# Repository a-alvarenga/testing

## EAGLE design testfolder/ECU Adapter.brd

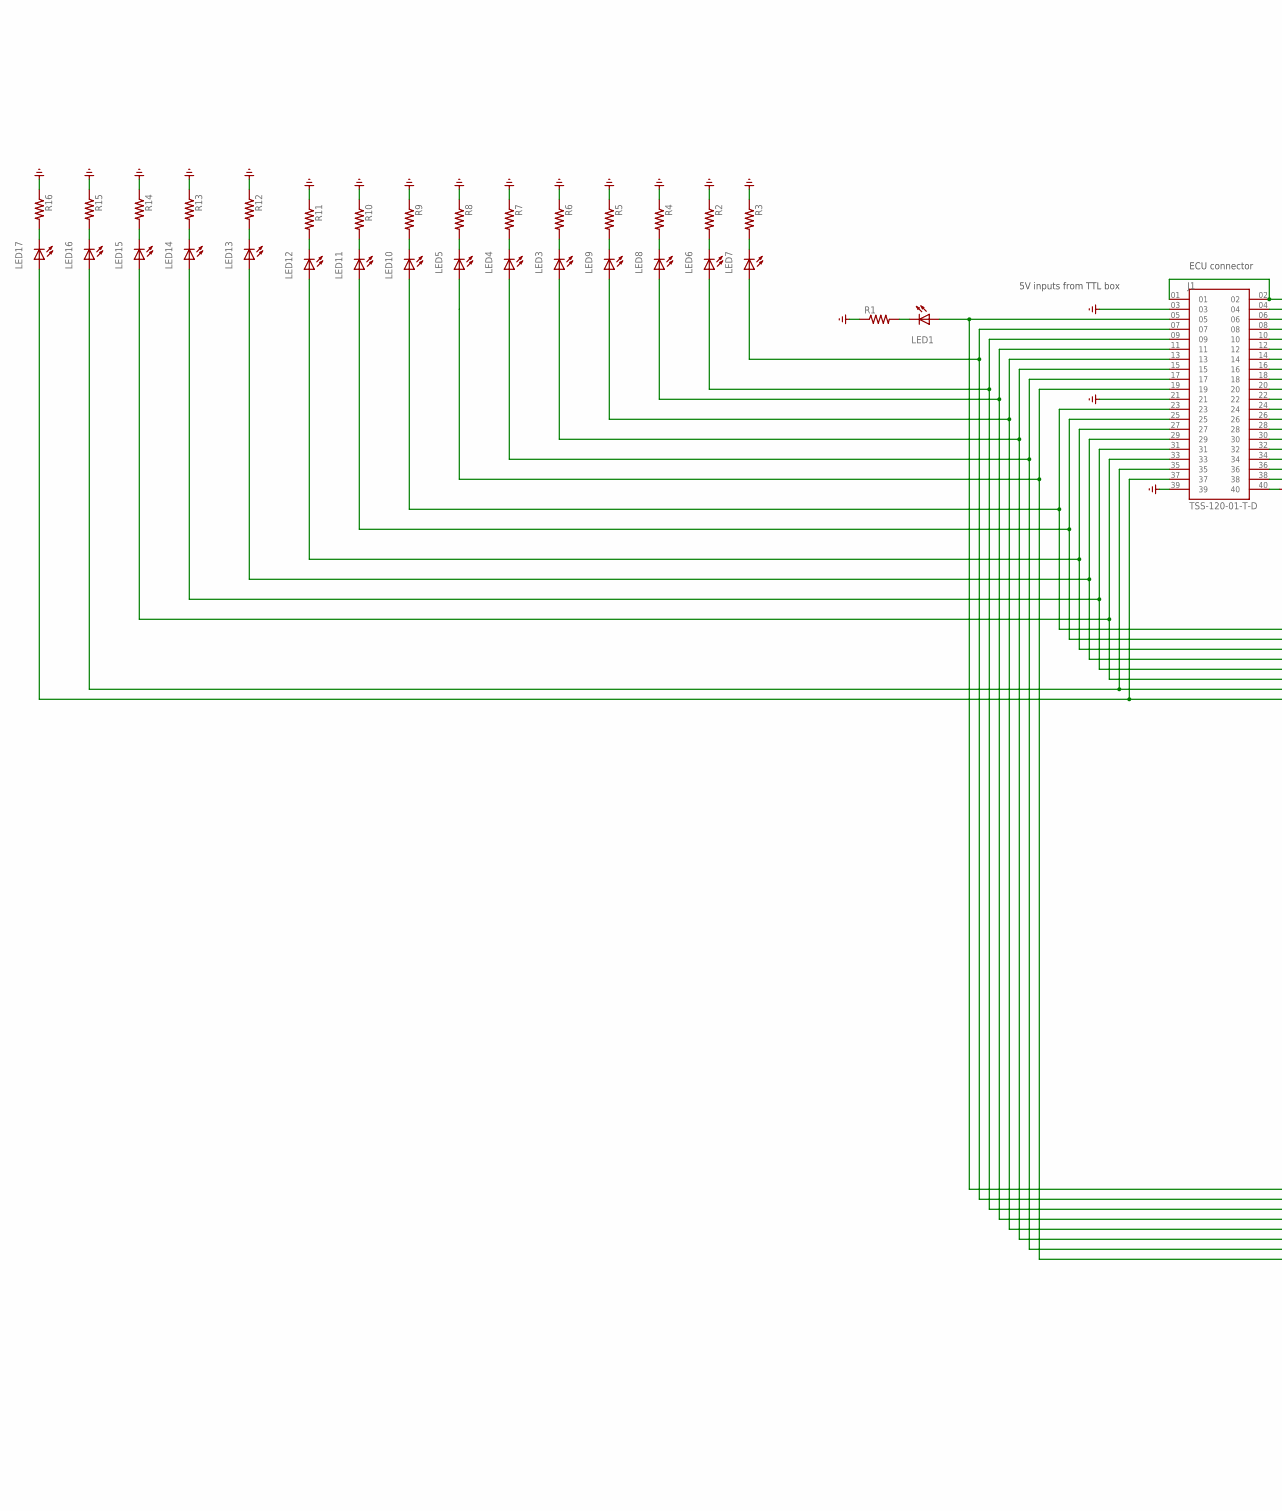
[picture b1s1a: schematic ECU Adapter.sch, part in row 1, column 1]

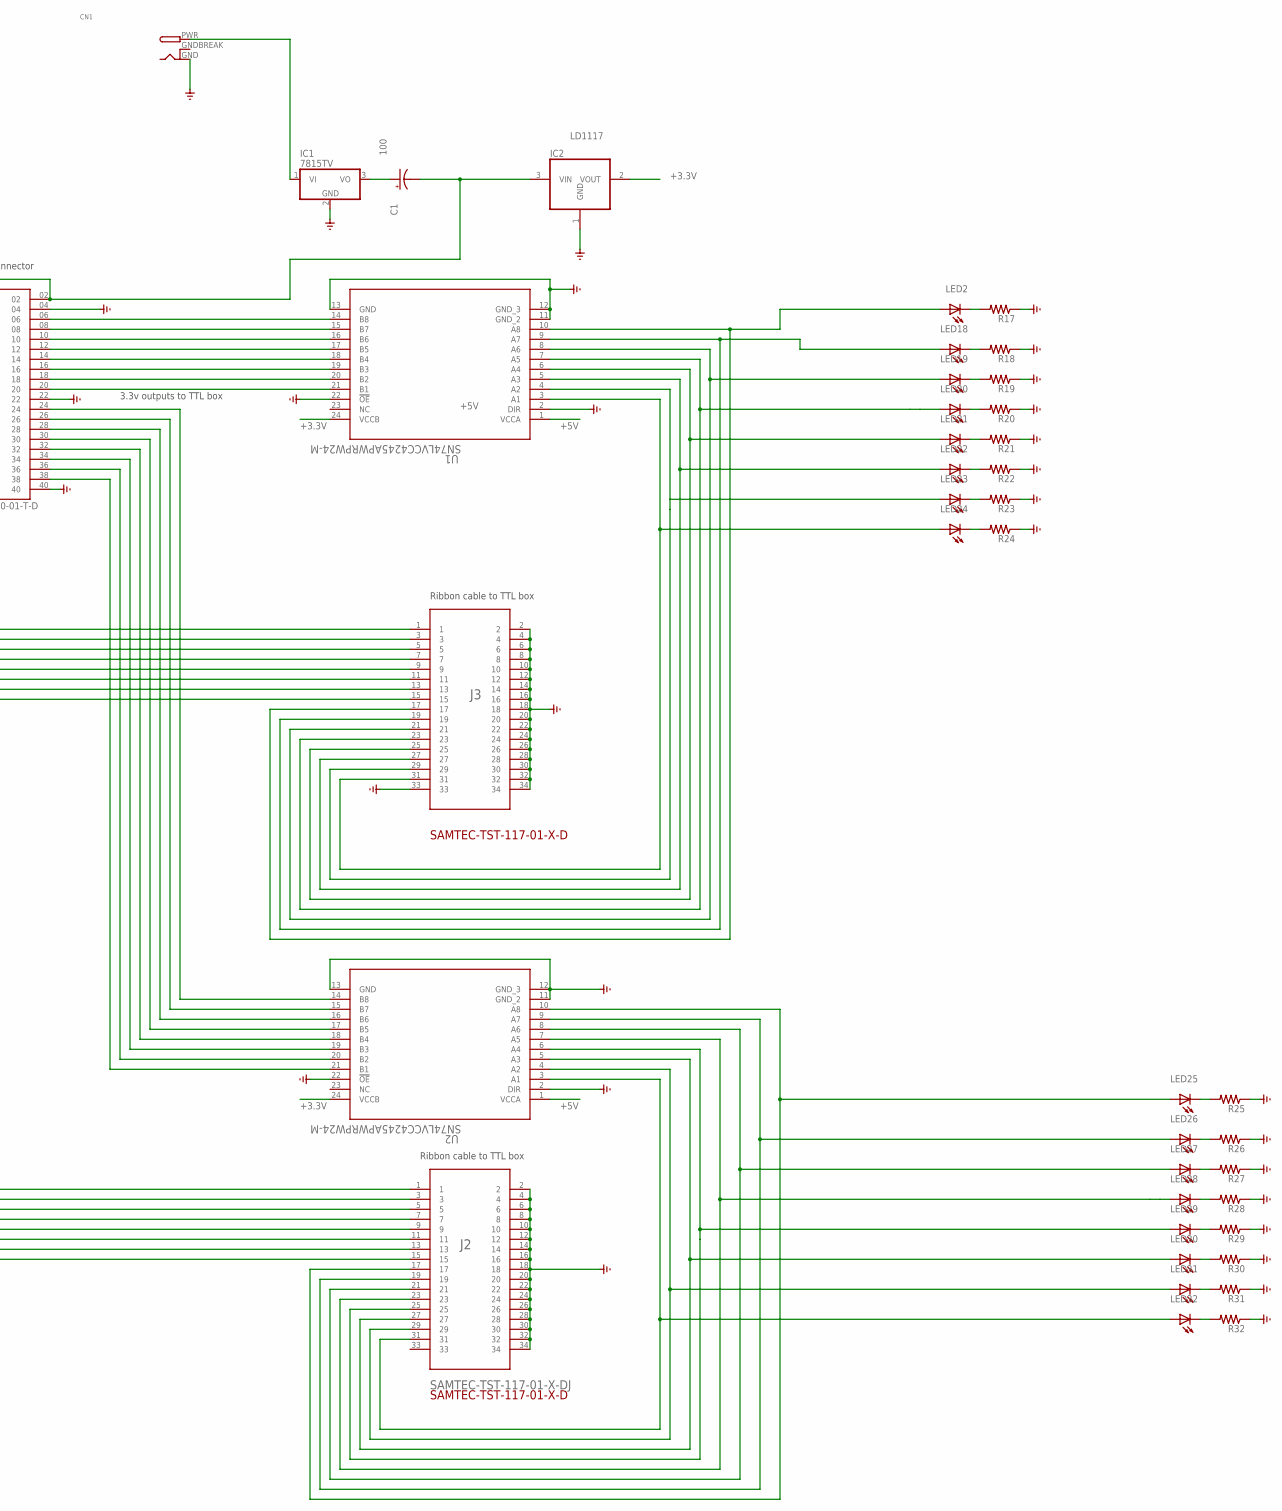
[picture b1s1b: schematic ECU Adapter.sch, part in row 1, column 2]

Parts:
C1: 100; E3,5-10
CN1: DCBARRELPTH; DCJACK_2MM_PTH
IC1: 7815TV; TO220V
IC2: LD1117; SOT223
J1: TSS-120-01-T-D; SAMTEC_TSS-120-01-T-D
J2, J3: SAMTEC-TST-117-01-X-DJ; SAMTEC-TST-117-01-X-D
LED1, LED2, LED3, LED4, LED5, LED6, LED7, LED8, LED9, LED10, LED11, LED12, LED13, LED14, LED15, LED16, LED17, LED18, LED19, LED20, LED21, LED22, LED23, LED24, LED25, LED26, LED27, LED28, LED29, LED30, LED31, LED32: LEDCHIPLED_0603; CHIPLED_0603
R1, R2, R3, R4, R5, R6, R7, R8, R9, R10, R11, R12, R13, R14, R15, R16, R17, R18, R19, R20, R21, R22, R23, R24, R25, R26, R27, R28, R29, R30, R31, R32: R-US_R0603; R0603
U1, U2: SN74LVCC4245APWRPW24-M; PW24-M

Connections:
+3.3V: IC2.2 (VOUT), U1.24 (VCCB), U2.24 (VCCB)
+5V: C1.-, IC2.3 (VIN), J1.01, J1.02, U1.1 (VCCA), U2.1 (VCCA)
GND: CN1.GND, IC1.2 (GND), IC2.1 (GND), J1.03, J1.04, J1.21, J1.22, J1.39, J1.40, J2.2, J2.4, J2.6, J2.8, J2.10, J2.12, J2.14, J2.16, J2.18, J2.20, J2.22, J2.24, J2.26, J2.28, J2.30, J2.32, J2.34, J3.2, J3.4, J3.6, J3.8, J3.10, J3.12, J3.14, J3.16, J3.18, J3.20, J3.22, J3.24, J3.26, J3.28, J3.30, J3.32, J3.33, J3.34, R1.1, R2.1, R3.1, R4.1, R5.1, R6.1, R7.1, R8.1, R9.1, R10.1, R11.1, R12.1, R13.1, R14.1, R15.1, R16.1, R17.1, R18.1, R19.1, R20.1, R21.1, R22.1, R23.1, R24.1, R25.1, R26.1, R27.1, R28.1, R29.1, R30.1, R31.1, R32.1, U1.2 (DIR), U1.11 (GND_2), U1.12 (GND_3), U1.13 (GND), U1.22 (!OE), U2.2 (DIR), U2.11 (GND_2), U2.12 (GND_3), U2.13 (GND), U2.22 (!OE)
GNDBREAK: CN1.GNDBREAK
unnamed: CN1.PWR, IC1.1 (VI)
unnamed: C1.+, IC1.3 (VO)
unnamed: J2.17, LED25.A, U2.10 (A8)
unnamed: LED25.C, R25.2
unnamed: LED26.C, R26.2
unnamed: J1.06, U1.14 (B8)
unnamed: J1.08, U1.15 (B7)
unnamed: J1.10, U1.16 (B6)
unnamed: J1.12, U1.17 (B5)
unnamed: J1.14, U1.18 (B4)
unnamed: J1.16, U1.19 (B3)
unnamed: J1.18, U1.20 (B2)
unnamed: J1.20, U1.21 (B1)
unnamed: LED27.C, R27.2
unnamed: J1.24, U2.14 (B8)
unnamed: J1.26, U2.15 (B7)
unnamed: J1.28, U2.16 (B6)
unnamed: J1.05, J2.1, LED1.A
unnamed: J1.29, J3.7, LED13.A
unnamed: LED13.C, R12.2
unnamed: J1.31, J3.9, LED14.A
unnamed: LED14.C, R13.2
unnamed: J1.33, J3.11, LED15.A
unnamed: LED15.C, R14.2
unnamed: J1.35, J3.13, LED16.A
unnamed: J2.19, LED26.A, U2.9 (A7)
unnamed: J2.21, LED27.A, U2.8 (A6)
unnamed: J2.25, LED29.A, U2.6 (A4)
unnamed: J2.27, LED30.A, U2.5 (A3)
unnamed: J2.29, LED31.A, U2.4 (A2)
unnamed: J2.31, LED32.A, U2.3 (A1)
unnamed: LED16.C, R15.2
unnamed: J3.17, LED2.A, U1.10 (A8)
unnamed: LED17.C, R16.2
unnamed: LED2.C, R17.2
unnamed: J2.23, LED28.A, U2.7 (A5)
unnamed: LED18.C, R18.2
unnamed: J3.21, LED19.A, U1.8 (A6)
unnamed: J1.37, J3.15, LED17.A
unnamed: J1.30, U2.17 (B5)
unnamed: J3.19, LED18.A, U1.9 (A7)
unnamed: J1.32, U2.18 (B4)
unnamed: LED28.C, R28.2
unnamed: J1.34, U2.19 (B3)
unnamed: J1.36, U2.20 (B2)
unnamed: J1.38, U2.21 (B1)
unnamed: LED1.C, R1.2
unnamed: J1.09, J2.5, LED6.A
unnamed: LED6.C, R2.2
unnamed: J1.07, J2.3, LED7.A
unnamed: LED7.C, R3.2
unnamed: J1.11, J2.7, LED8.A
unnamed: LED8.C, R4.2
unnamed: J1.13, J2.9, LED9.A
unnamed: LED9.C, R5.2
unnamed: J1.15, J2.11, LED3.A
unnamed: LED3.C, R6.2
unnamed: J1.17, J2.13, LED4.A
unnamed: LED4.C, R7.2
unnamed: J1.19, J2.15, LED5.A
unnamed: LED5.C, R8.2
unnamed: J1.23, J3.1, LED10.A
unnamed: LED10.C, R9.2
unnamed: J1.25, J3.3, LED11.A
unnamed: LED11.C, R10.2
unnamed: J1.27, J3.5, LED12.A
unnamed: LED12.C, R11.2
unnamed: LED19.C, R19.2
unnamed: J3.23, LED20.A, U1.7 (A5)
unnamed: LED20.C, R20.2
unnamed: J3.25, LED21.A, U1.6 (A4)
unnamed: LED21.C, R21.2
unnamed: J3.27, LED22.A, U1.5 (A3)
unnamed: LED22.C, R22.2
unnamed: J3.29, LED23.A, U1.4 (A2)
unnamed: LED23.C, R23.2
unnamed: J3.31, LED24.A, U1.3 (A1)
unnamed: LED24.C, R24.2
unnamed: LED29.C, R29.2
unnamed: LED30.C, R30.2
unnamed: LED31.C, R31.2
unnamed: LED32.C, R32.2

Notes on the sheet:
3.3v outputs to TTL box
5V inputs from TTL box
ECU connector
Ribbon cable to TTL box

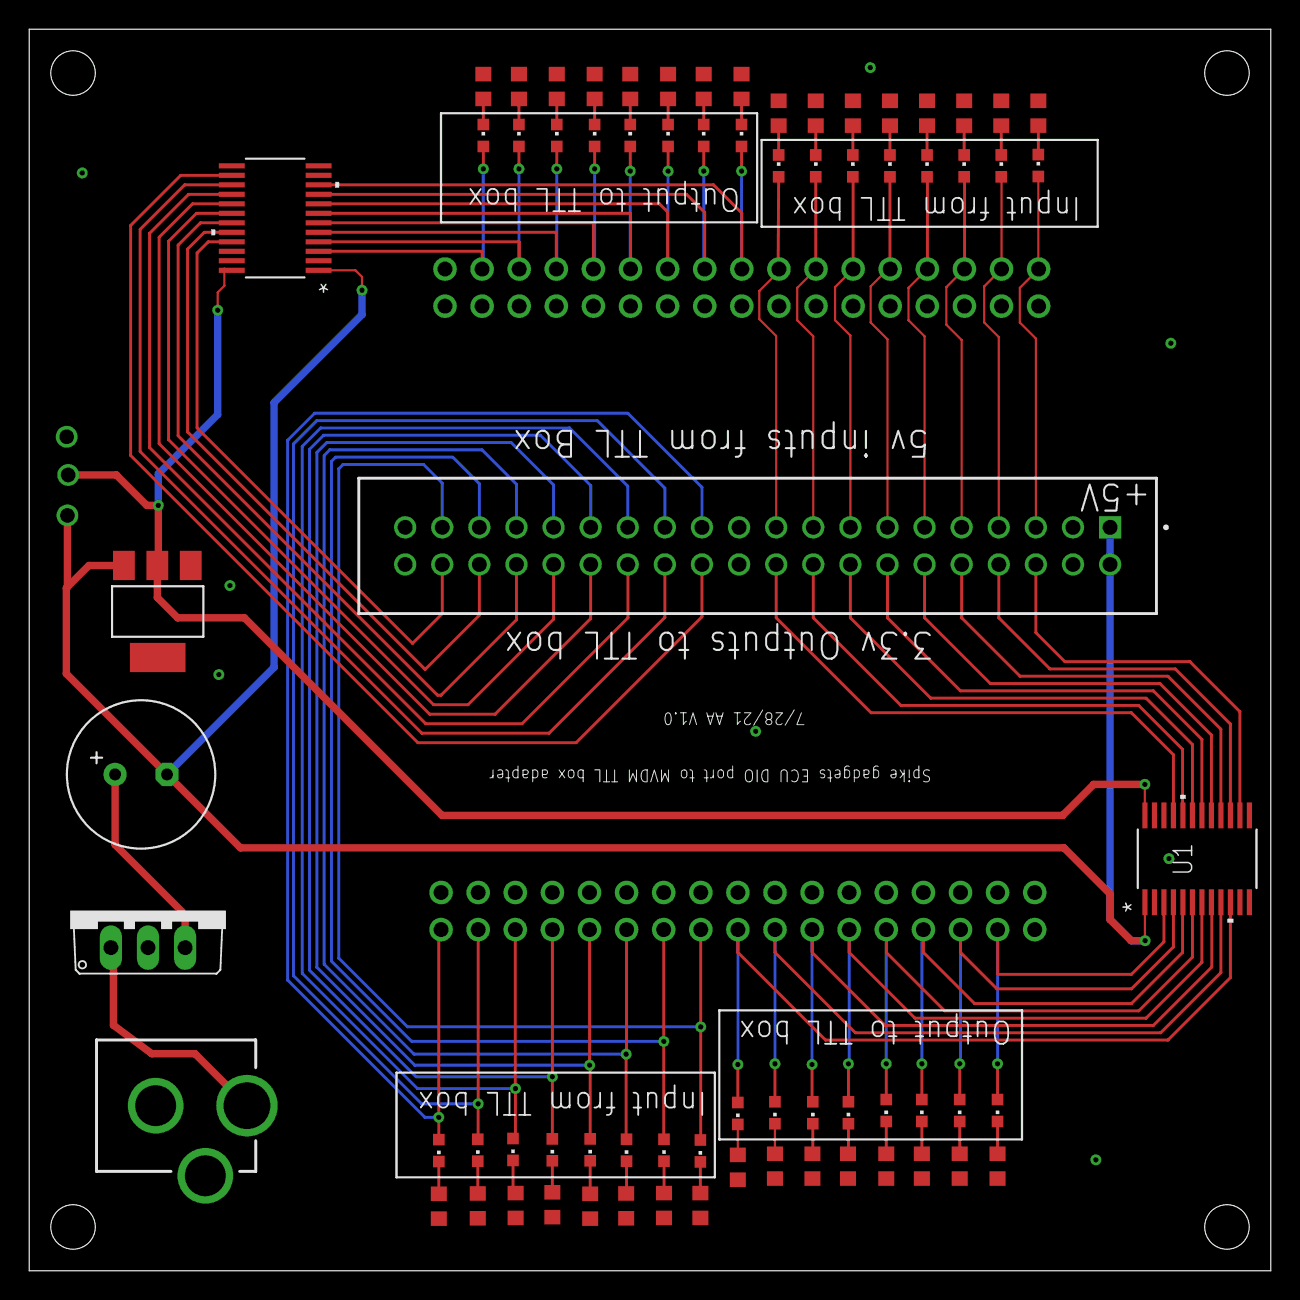
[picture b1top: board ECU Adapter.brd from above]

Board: 2 copper layers, 85.0 x 85.0 mm, 73 parts (0 on the bottom side), 85 nets.

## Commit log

2018-01-11 Added shared black drive files
2018-01-11 Changed dim on MillMax pin
    Previous version of pin was too short, so updated to 1.9 mm
2021-07-30 reamde
    dsaf
